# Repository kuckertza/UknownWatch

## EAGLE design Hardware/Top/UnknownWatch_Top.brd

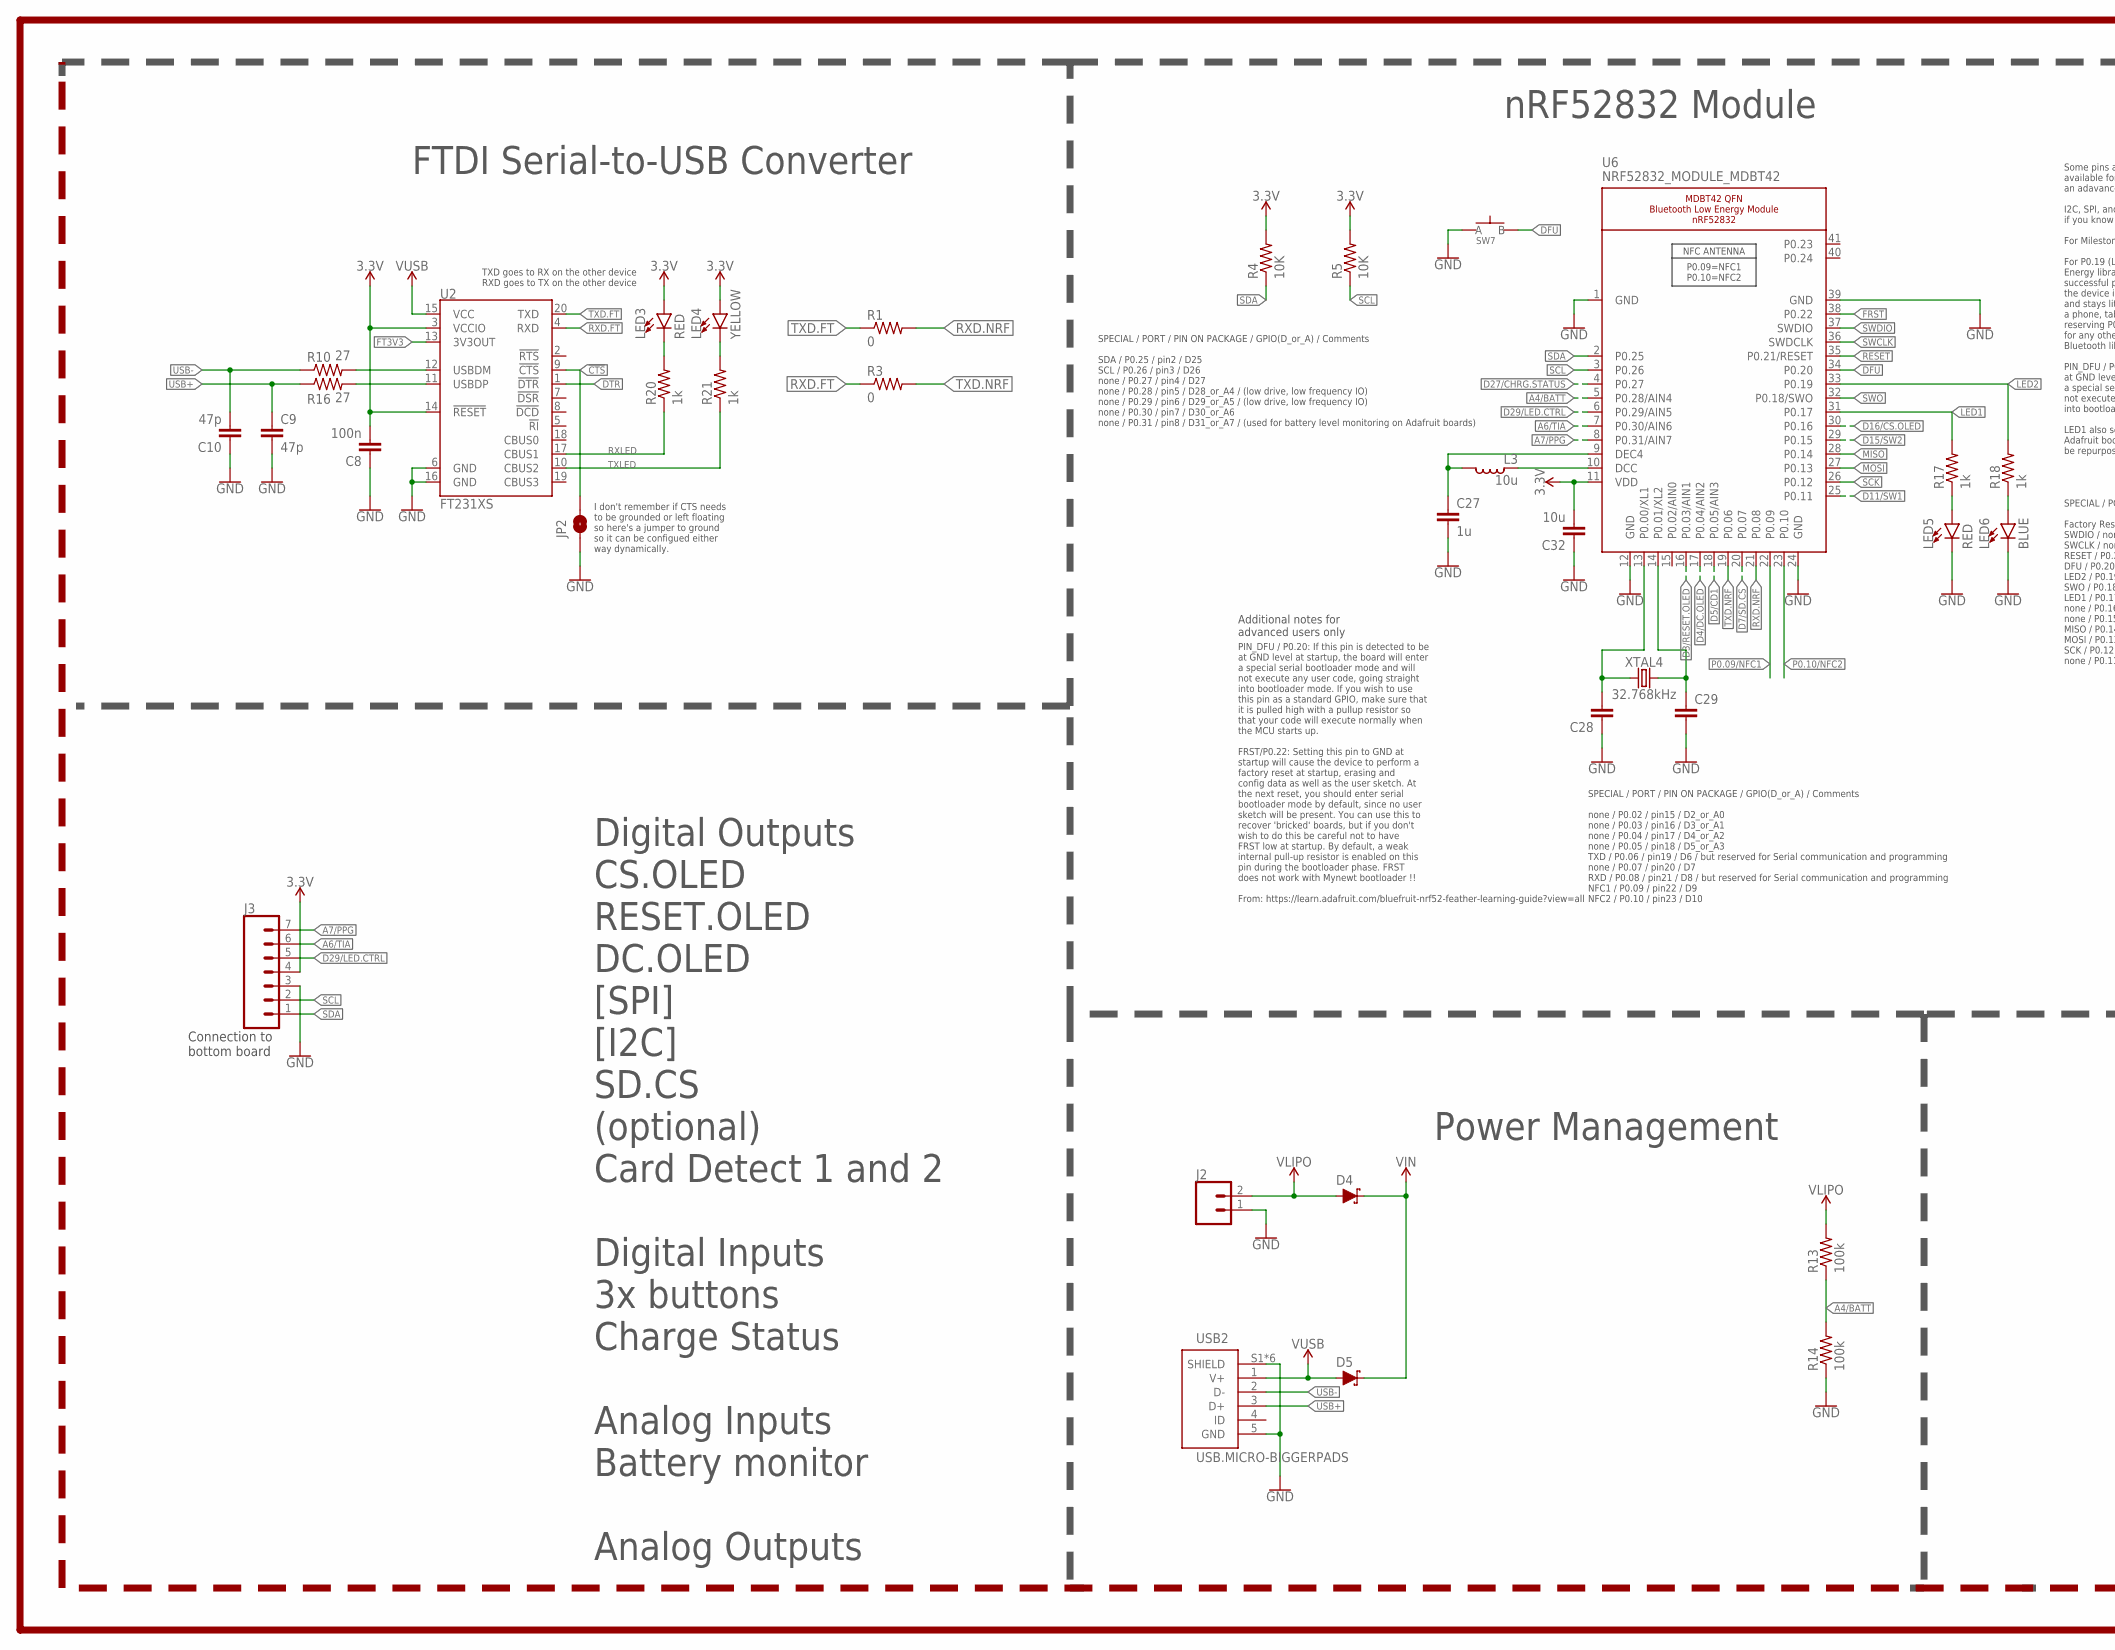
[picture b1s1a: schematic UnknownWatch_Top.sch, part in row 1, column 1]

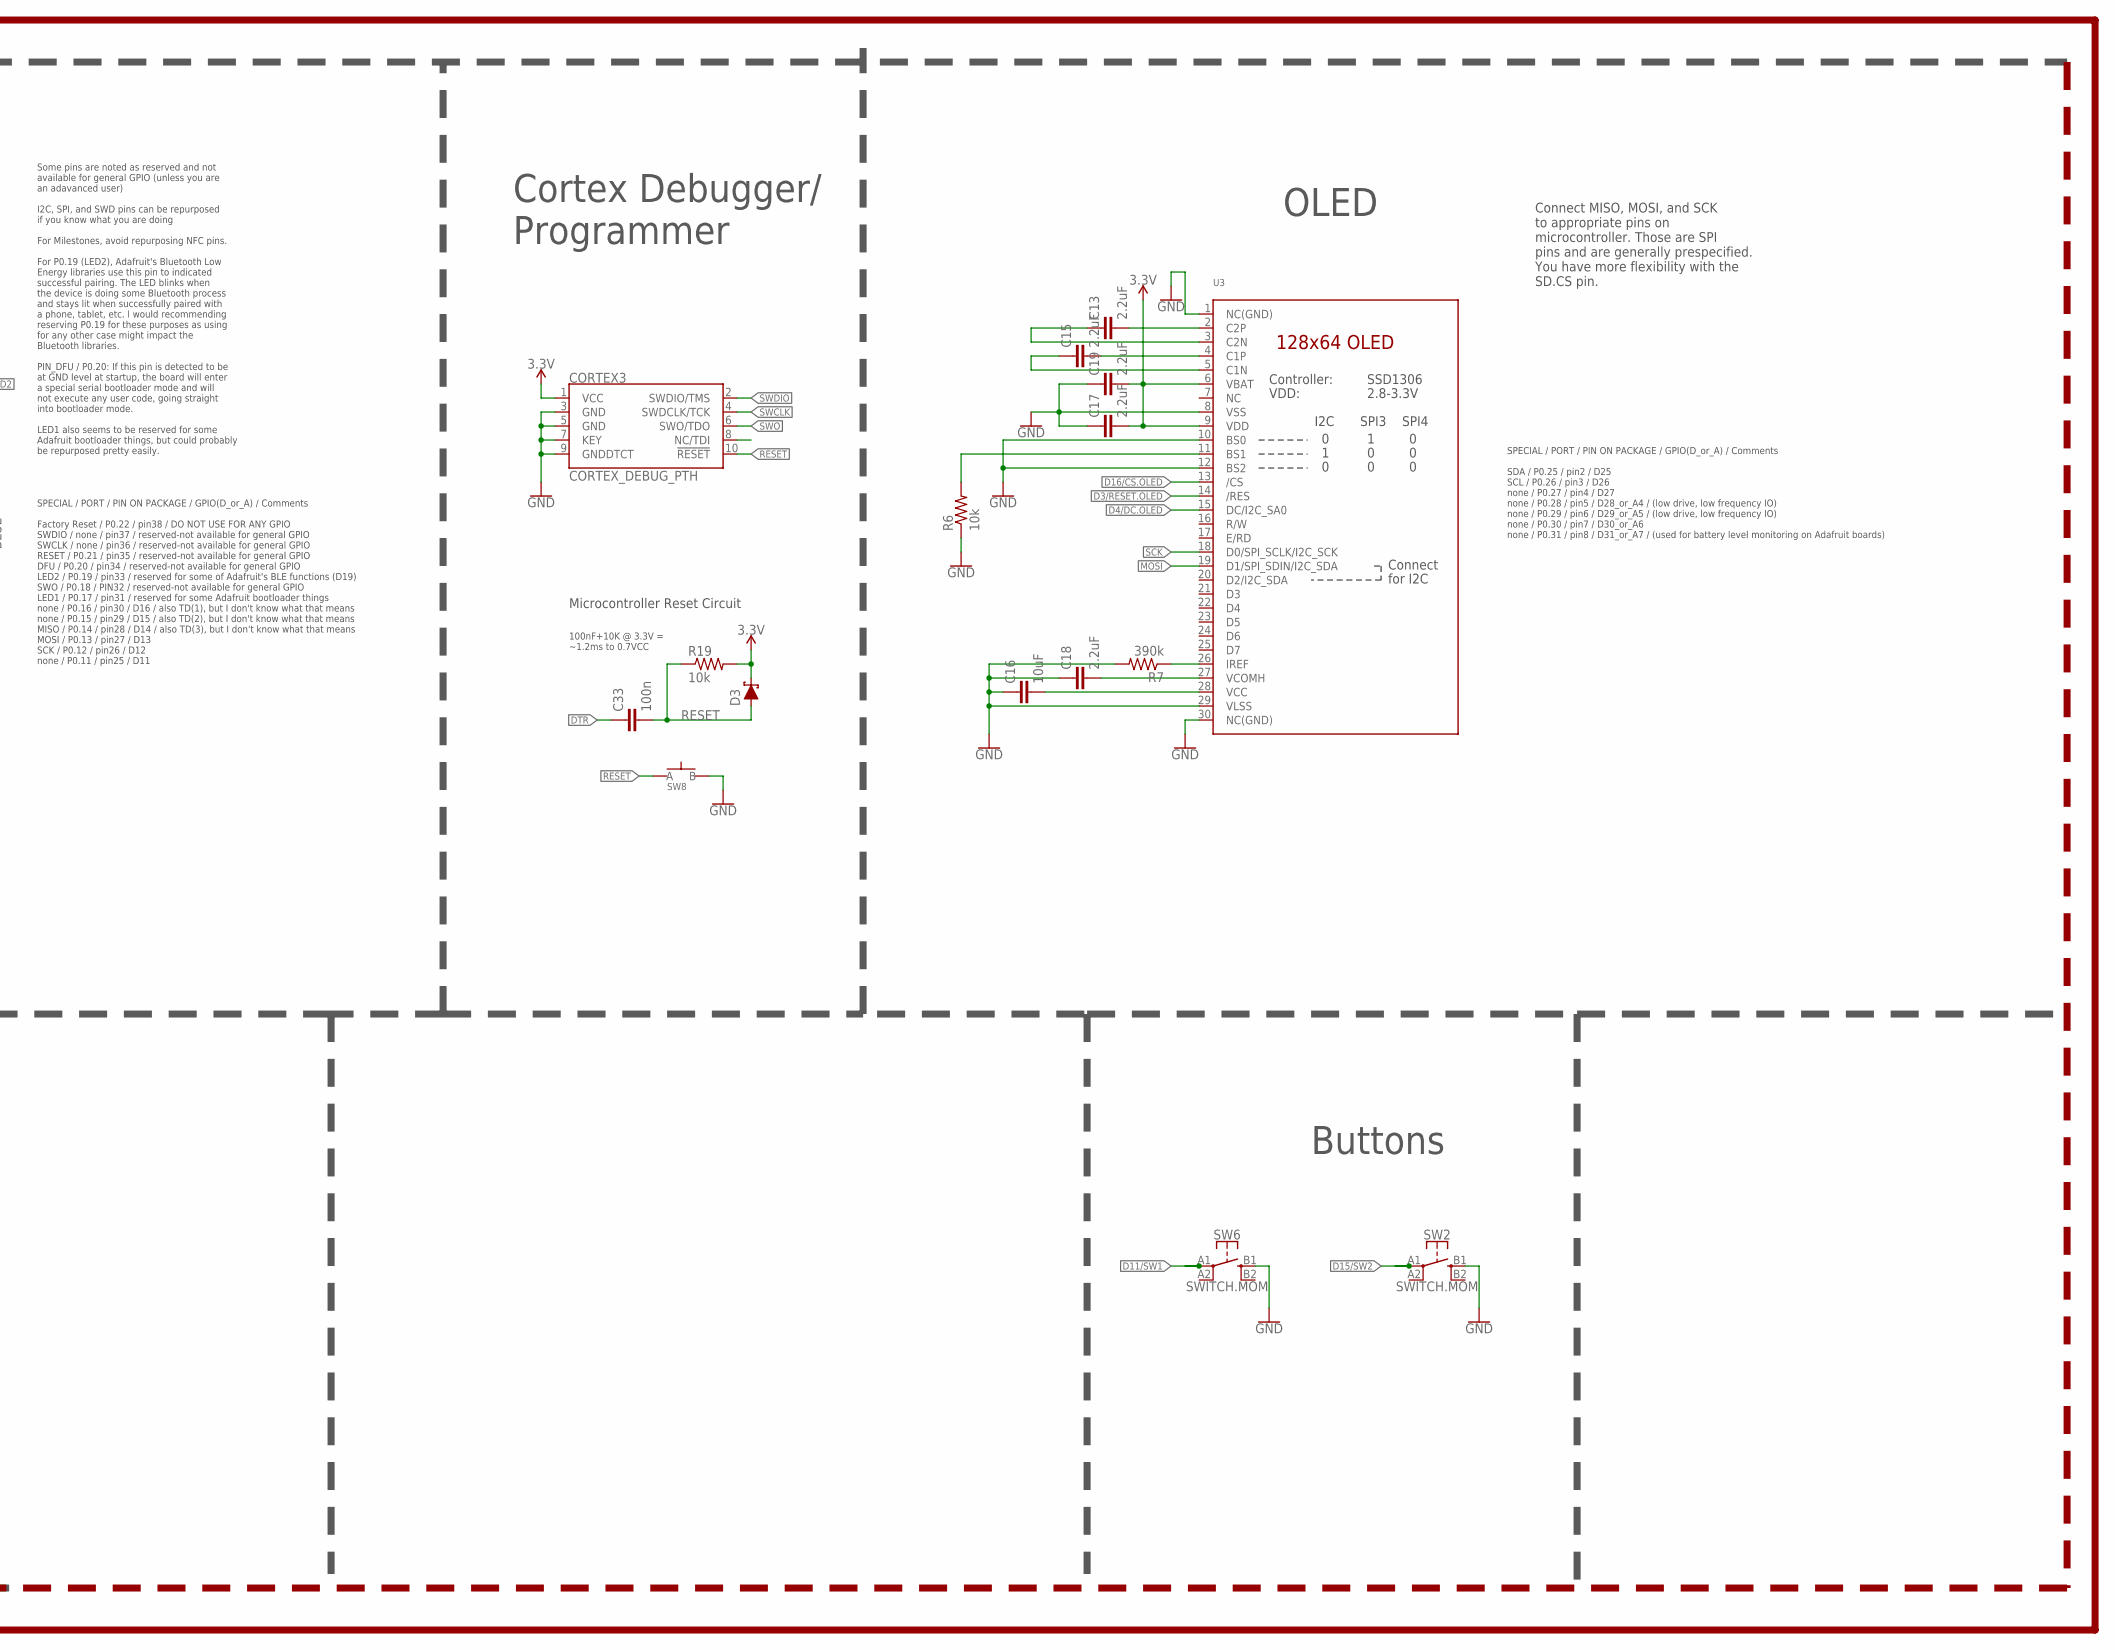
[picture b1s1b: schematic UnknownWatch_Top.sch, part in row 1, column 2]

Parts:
C8, C33: 100n; C0603
C9, C10: 47p; C0603
C13, C15, C17, C18, C19: 2.2uF; C0402
C16: 10uF; C0603
C27: 1u; C0603
C28, C29: CAPACITOR0603; C0603
C32: 10u; C0805
CORTEX3: CORTEX_DEBUG_PTH; 2X5-PTH-1.27MM
D3, D4, D5: SCHOTTKY-USC; USC
J2: CONN_02; 1X02
J3: CONN_07-1.27MM; 1X07_1.27MM
JP2: JUMPER-SMT_2_NO_SILK; SMT-JUMPER_2_NO_SILK
L3: 10u; L0603
LED3, LED5: RED; LED-0603
LED4: YELLOW; LED-0603
LED6: BLUE; LED-0603
R1, R3: 0; R0603
R4, R5: 10K; R0603
R6, R19: 10k; R0603
R7: 390k; R0603
R10, R16: 27; R0603
R13, R14: 100k; R0603
R17, R18, R20, R21: 1k; R0603
SW2, SW6: SWITCH.MOM; TACTILE_SWITCH_SMD_6.2MM_TALL
SW7, SW8: SPST-PTS830GG140-COPY.1-3; BUTTON-GULLWING
U2: FT231XS; SSOP20_L
U3: DISP_OLED_UG-2864HSWEG01-NO-WRAPAROUND; UG-2864HSWEG01_0.96IN_NO-WRAPAROUND
U6: NRF52832_MODULE_MDBT42; BLE_MODULE_RAYTAC_MDBT42
USB2: USB.MICRO-BIGGERPADS; USB-MICRO-01.BIGGERPADS
XTAL4: 32.768kHz; 2-SMD.NOLEAD.2.0MMTO1.2MM

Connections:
3.3V: C8.2, C17.2, C19.2, C32.2, CORTEX3.1 (VCC), D3.- (C), J3.4, LED3.A, LED4.A, R4.2, R5.2, R19.2, U2.3 (VCCIO), U2.14 (!RESET), U3.6 (VBAT), U3.9 (VDD), U6.11 (VDD)
!CTS: JP2.2, U2.9 (!CTS)
A4/BATT: R13.1, R14.2, U6.5 (P0.28/AIN4)
A6/TIA: J3.6, U6.7 (P0.30/AIN6)
A7/PPG: J3.7, U6.8 (P0.31/AIN7)
D3/RESET.OLED: U3.14 (/RES), U6.16 (P0.03/AIN1)
D4/DC.OLED: U3.15 (DC/I2C_SA0), U6.17 (P0.04/AIN2)
D5/CD1: U6.18 (P0.05/AIN3)
D7/SD.CS: U6.20 (P0.07)
D11/SW1: SW6.A1 (1), U6.25 (P0.11)
D15/SW2: SW2.A1 (1), U6.29 (P0.15)
D16/CS.OLED: U3.13 (/CS), U6.30 (P0.16)
D27/CHRG.STATUS: U6.4 (P0.27)
D29/LED.CTRL: J3.5, U6.6 (P0.29/AIN5)
DFU: SW7.3 (B), U6.34 (P0.20)
DTR: C33.1, U2.1 (!DTR)
FRST: U6.38 (P0.22)
FT3V3: U2.13 (3V3OUT)
GND: C8.1, C9.2, C10.1, C16.1, C17.1, C18.1, C19.1, C27.2, C28.1, C29.2, C32.1, CORTEX3.3 (GND), CORTEX3.5 (GND), CORTEX3.7 (KEY), CORTEX3.9 (GNDDTCT), J2.1, J3.3, JP2.1, LED5.C, LED6.C, R6.1, R7.2, R14.1, SW2.B1 (3), SW6.B1 (3), SW7.1 (A), SW8.3 (B), U2.6 (GND), U2.16 (GND), U3.1 (NC(GND)), U3.8 (VSS), U3.10 (BS0), U3.12 (BS2), U3.29 (VLSS), U3.30 (NC(GND)), U6.1 (GND), U6.12 (GND), U6.24 (GND), U6.39 (GND), USB2.5 (GND), USB2.S1 (SHIELD), USB2.S2 (SHIELD), USB2.S3 (SHIELD), USB2.S4 (SHIELD), USB2.S5 (SHIELD), USB2.S6 (SHIELD)
LED1: R17.2, U6.31 (P0.17)
LED2: R18.2, U6.33 (P0.19)
MISO: U6.28 (P0.14)
MOSI: U3.19 (D1/SPI_SDIN/I2C_SDA), U6.27 (P0.13)
unnamed: R6.2, U3.11 (BS1)
unnamed: R7.1, U3.26 (IREF)
unnamed: C13.2, U3.2 (C2P)
unnamed: C13.1, U3.3 (C2N)
unnamed: C15.2, U3.4 (C1P)
unnamed: C15.1, U3.5 (C1N)
unnamed: R10.2, U2.12 (USBDM)
unnamed: R16.2, U2.11 (USBDP)
unnamed: C16.2, U3.28 (VCC)
unnamed: LED3.C, R20.2
unnamed: C18.2, U3.27 (VCOMH)
unnamed: LED4.C, R21.2
unnamed: C28.2, U6.13 (P0.00/XL1), XTAL4.P$1 (1)
unnamed: C29.1, U6.14 (P0.01/XL2), XTAL4.P$2 (2)
unnamed: LED5.A, R17.1
unnamed: LED6.A, R18.1
unnamed: L3.1, U6.10 (DCC)
unnamed: C27.1, L3.2, U6.9 (DEC4)
P0.09/NFC1: U6.22 (P0.09)
P0.10/NFC2: U6.23 (P0.10)
RESET: C33.2, CORTEX3.10 (!RESET), D3.+ (A), R19.1, SW8.1 (A), U6.35 (P0.21/RESET)
RXD.FT: R3.1, U2.4 (RXD)
RXD.NRF: R1.2, U6.21 (P0.08)
RXLED: R20.1, U2.17 (CBUS1)
SCK: U3.18 (D0/SPI_SCLK/I2C_SCK), U6.26 (P0.12)
SCL: J3.2, R5.1, U6.3 (P0.26)
SDA: J3.1, R4.1, U6.2 (P0.25)
SWCLK: CORTEX3.4 (SWDCLK/TCK), U6.36 (SWDCLK)
SWDIO: CORTEX3.2 (SWDIO/TMS), U6.37 (SWDIO)
SWO: CORTEX3.6 (SWO/TDO), U6.32 (P0.18/SWO)
TXD.FT: R1.1, U2.20 (TXD)
TXD.NRF: R3.2, U6.19 (P0.06)
TXLED: R21.1, U2.10 (CBUS2)
USB+: C9.1, R16.1, USB2.3 (D+)
USB-: C10.2, R10.1, USB2.2 (D-)
VIN: D4.- (C), D5.- (C)
VLIPO: D4.+ (A), J2.2, R13.2
V_USB: D5.+ (A), U2.15 (VCC), USB2.1 (V+)

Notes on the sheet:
SPECIAL / PORT / PIN ON PACKAGE / GPIO(D_or_A) / Comments SDA / P0.25 / pin2 / D25 SCL / P0.26 / pin3 / D26 none / P0.27 / pin4 / D27 none / P0.28 / pin5 / D28_or_A4 / (low drive, low frequency IO) none / P0.29 / pin6 / D29_or_A5 / (low drive, low frequency IO) none / P0.30 / pin7 / D30_or_A6 none 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
Connect MISO, MOSI, and SCK to appropriate pins on microcontroller. Those are SPI pins and are generally prespecified. You have more flexibility with the SD.CS pin.
nRF52832 Module
OLED
Power Management
Buttons
Cortex Debugger/ Programmer
Digital Outputs CS.OLED RESET.OLED DC.OLED [SPI] [I2C] SD.CS (optional) Card Detect 1 and 2 Digital Inputs 3x buttons Charge Status Analog Inputs Battery monitor Analog Outputs
Microcontroller Reset Circuit
100nF+10K @ 3.3V = ~1.2ms to 0.7VCC
SPECIAL / PORT / PIN ON PACKAGE / GPIO(D_or_A) / Comments none / P0.02 / pin15 / D2_or_A0 none / P0.03 / pin16 / D3_or_A1 none / P0.04 / pin17 / D4_or_A2 none / P0.05 / pin18 / D5_or_A3 TXD / P0.06 / pin19 / D6 / but reserved for Serial communication and programming none / P0.07 / pin20 / D7 RXD / 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
SPECIAL / PORT / PIN ON PACKAGE / GPIO(D_or_A) / Comments Factory Reset / P0.22 / pin38 / DO NOT USE FOR ANY GPIO SWDIO / none / pin37 / reserved-not available for general GPIO SWCLK / none / pin36 / reserved-not available for general GPIO RESET / P0.21 / pin35 / reserved-not available for general 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
Some pins are noted as reserved and not available for general GPIO (unless you are an adavanced user) I2C, SPI, and SWD pins can be repurposed if you know what you are doing For Milestones, avoid repurposing NFC pins. For P0.19 (LED2), Adafruit's Bluetooth Low Energy libraries use this pin to indic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
PIN_DFU / P0.20: If this pin is detected to be at GND level at startup, the board will enter a special serial bootloader mode and will not execute any user code, going straight into bootloader mode. If you wish to use this pin as a standard GPIO, make sure that it is pulled high with a pullup resis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
Additional notes for advanced users only
TXD goes to RX on the other device RXD goes to TX on the other device
I don't remember if CTS needs to be grounded or left floating so here's a jumper to ground so it can be configued either way dynamically.
FTDI Serial-to-USB Converter
Connection to bottom board

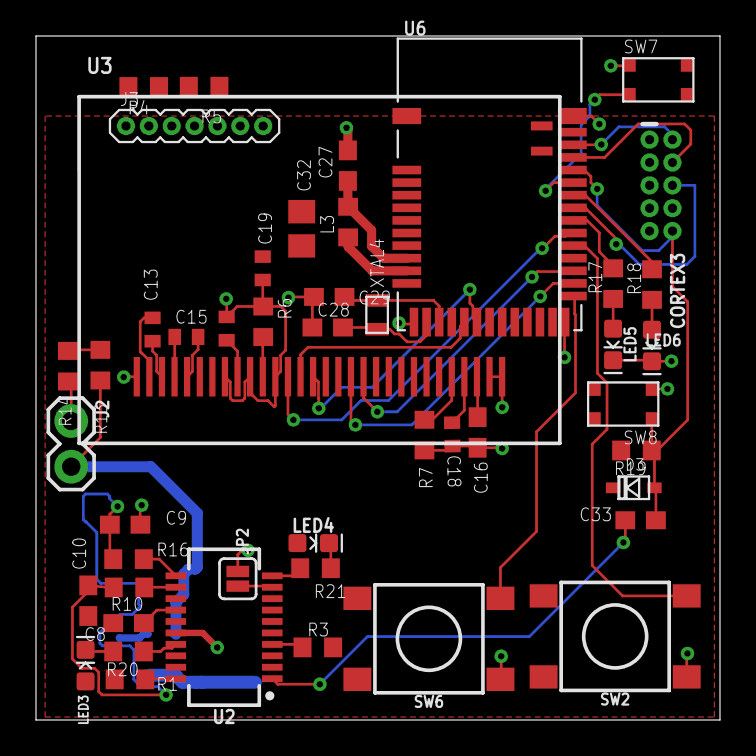
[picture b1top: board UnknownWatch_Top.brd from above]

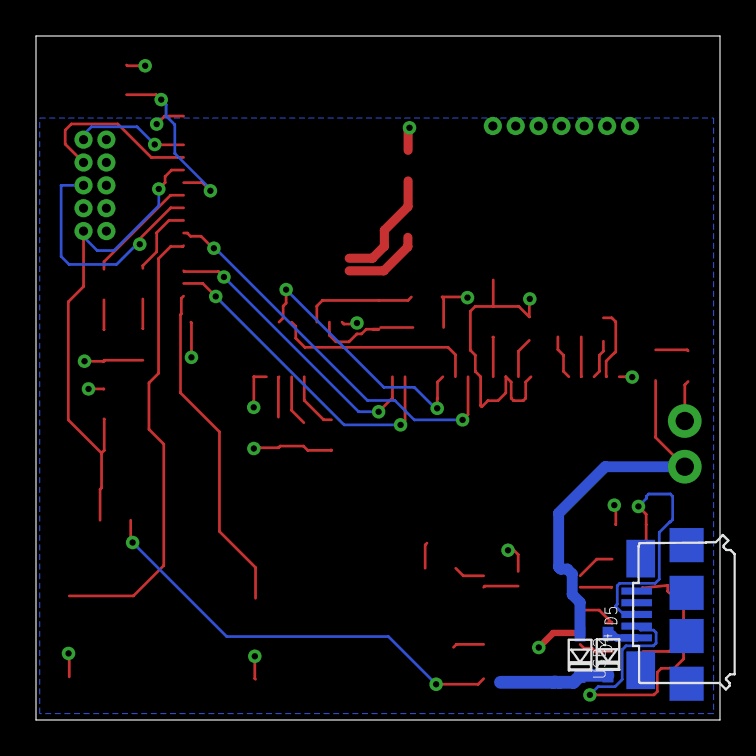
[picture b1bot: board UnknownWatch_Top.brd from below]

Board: 2 copper layers, 38.0 x 38.0 mm, 50 parts (3 on the bottom side), 53 nets.

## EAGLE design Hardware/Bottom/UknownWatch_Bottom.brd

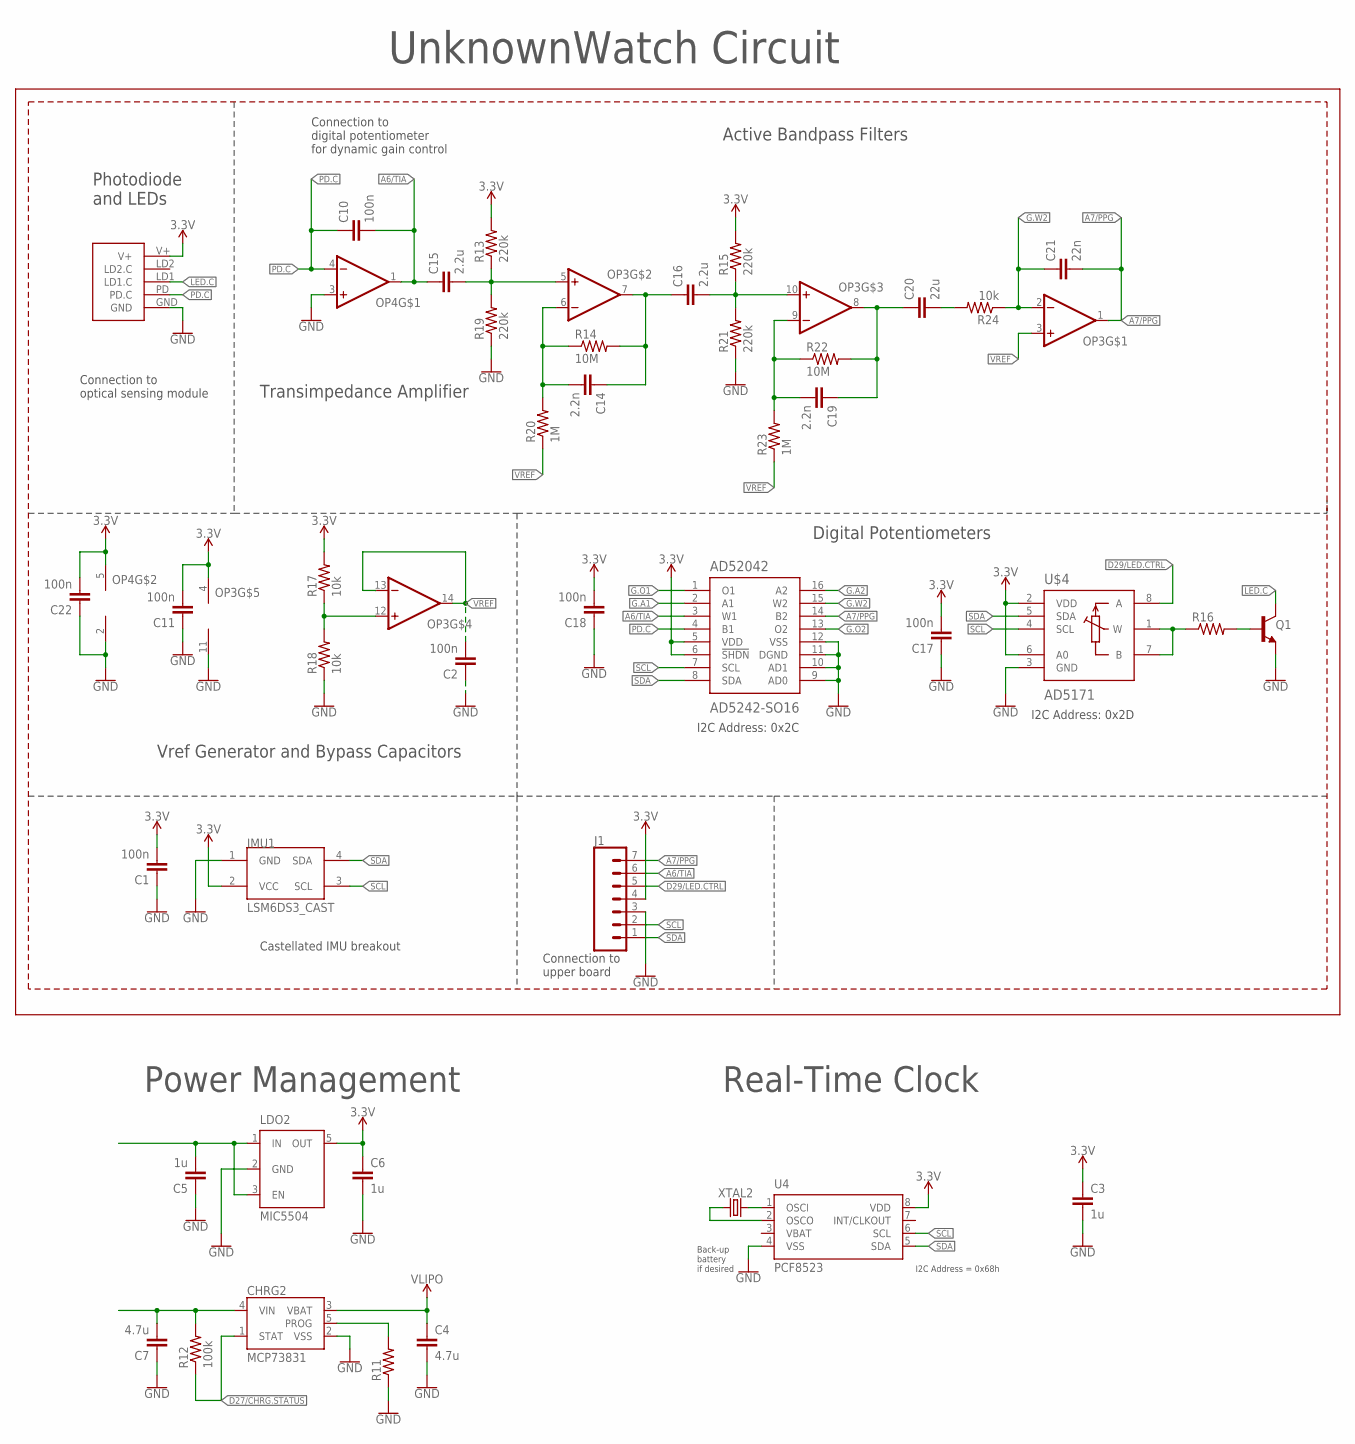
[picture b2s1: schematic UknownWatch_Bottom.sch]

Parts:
AD52042: AD5242-SO16; SO16
C1, C2, C10, C11, C17, C18, C22: 100n; C0603
C3, C5, C6: 1u; C0603
C4, C7: 4.7u; C0603
C14, C19: 2.2n; C0603
C15, C16: 2.2u; C0603
C20: 22u; C0603
C21: 22n; C0603
CHRG2: MCP73831; SOT23-5
IMU1: LSM6DS3_CAST
J1: CONN_07-1.27MM; 1X07_1.27MM
LDO2: MIC5504; SOT23-5
OP3: OP-QUAD-SO14; SO14
OP4: OP-SINGLEOT; SOT23-5
Q1: NPN-GENERIC; SOT23-3
R11, R16: RESISTOR0603; R0603
R12: 100k; R0603
R13, R15, R19, R21: 220k; R0603
R14, R22: 10M; R0603
R17, R18: 10k; R0402
R20, R23: 1M; R0603
R24: 10k; R0603
U4: PCF8523; SO8; DIGIKEY 568-5306-1-ND
U$3: PPG.MODULE.2
U$4: AD5171; SOT-23-8
XTAL2: 32.7680kHz; 2-SMD.NOLEAD.2.0MMTO1.2MM

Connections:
3.3V: AD52042.5 (VDD), AD52042.6 (!SHDN), C1.2, C3.1, C6.1, C11.2, C17.2, C18.2, C22.2, IMU1.2 (VCC), J1.4, LDO2.5 (OUT), OP3.4 (V+), OP4.5 (V+), R13.2, R15.2, R17.2, U4.8 (VDD), U$3.V+, U$4.2 (VDD), U$4.6 (A0)
A6/TIA: AD52042.3 (W1), C10.2, C15.1, J1.6, OP4.1 (OUT)
A7/PPG: AD52042.14 (B2), C21.2, J1.7, OP3.1 (OUT)
D27/CHRG.STATUS: CHRG2.1 (STAT), R12.1
D29/LED.CTRL: J1.5, U$4.8 (A)
G.A1: AD52042.2 (A1)
G.A2: AD52042.16 (A2)
G.O1: AD52042.1 (O1)
G.O2: AD52042.13 (O2)
G.W2: AD52042.15 (W2), C21.1, OP3.2 (-IN), R24.1
GND: AD52042.9 (AD0), AD52042.10 (AD1), AD52042.11 (DGND), AD52042.12 (VSS), C1.1, C2.1, C3.2, C4.2, C5.1, C6.2, C7.1, C11.1, C17.1, C18.1, C22.1, CHRG2.2 (VSS), IMU1.1 (GND), J1.3, LDO2.2 (GND), OP3.11 (V-), OP4.2 (V-), OP4.3 (+IN), Q1.2 (E), R11.1, R18.1, R19.1, R21.1, U4.4 (VSS), U$3.GND, U$4.3 (GND)
LED.C: Q1.3 (C), U$3.LD1 (LD1.C)
unnamed: U4.1 (OSCI), XTAL2.P$2 (2)
unnamed: CHRG2.5 (PROG), R11.2
unnamed: U4.2 (OSCO), XTAL2.P$1 (1)
unnamed: Q1.1 (B), R16.2
unnamed: R16.1, U$4.1 (W), U$4.7 (B)
unnamed: OP3.12 (+IN), R17.1, R18.2
unnamed: C15.2, OP3.5 (+IN), R13.1, R19.2
unnamed: C14.2, OP3.6 (-IN), R14.1, R20.2
unnamed: C14.1, C16.1, OP3.7 (OUT), R14.2
unnamed: C16.2, OP3.10 (+IN), R15.1, R21.2
unnamed: C19.2, OP3.9 (-IN), R22.1, R23.2
unnamed: C19.1, C20.1, OP3.8 (OUT), R22.2
unnamed: C20.2, R24.2
PD.C: AD52042.4 (B1), C10.1, OP4.4 (-IN), U$3.PD (PD.C)
SCL: AD52042.7 (SCL), IMU1.3 (SCL), J1.2, U4.6 (SCL), U$4.4 (SCL)
SDA: AD52042.8 (SDA), IMU1.4 (SDA), J1.1, U4.5 (SDA), U$4.5 (SDA)
VBAT: U4.3 (VBAT)
VIN: C5.2, C7.2, CHRG2.4 (VIN), LDO2.1 (IN), LDO2.3 (EN), R12.2
VLIPO: C4.1, CHRG2.3 (VBAT)
VREF: C2.2, OP3.3 (+IN), OP3.13 (-IN), OP3.14 (OUT), R20.1, R23.1

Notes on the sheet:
Photodiode and LEDs
Active Bandpass Filters
Digital Potentiometers
Transimpedance Amplifier
I2C Address: 0x2C
I2C Address: 0x2D
Vref Generator and Bypass Capacitors
Connection to optical sensing module
Connection to digital potentiometer for dynamic gain control
Connection to upper board
Castellated IMU breakout
UnknownWatch Circuit
Real-Time Clock
I2C Address = 0x68h
Back-up battery if desired
Power Management

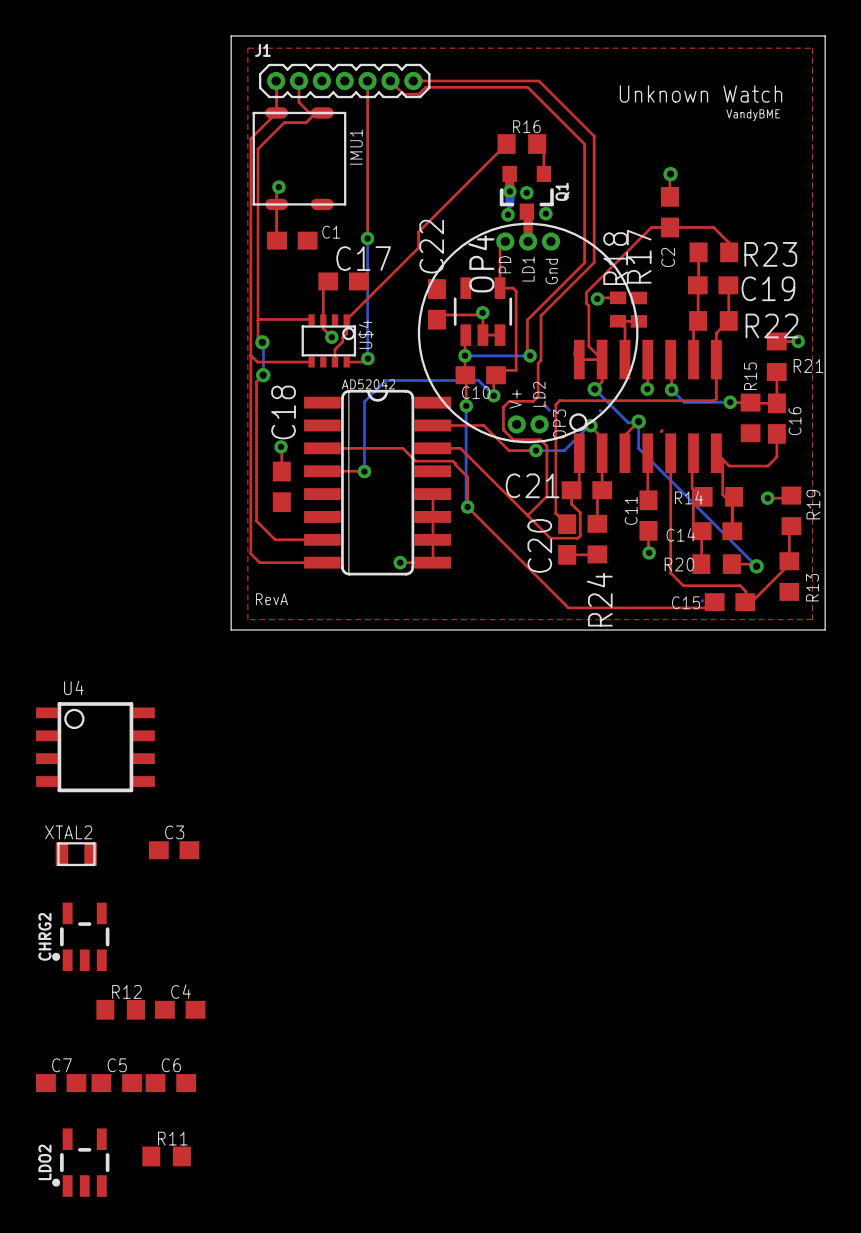
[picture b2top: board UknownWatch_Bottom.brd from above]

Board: 2 copper layers, 33.0 x 33.0 mm, 45 parts (0 on the bottom side), 27 nets.

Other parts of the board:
U$1: REV.A

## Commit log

2020-06-04 Added and Organized Files
2020-06-09 Added various compnents to top layer of device
2020-06-11 Adde Buttons
2020-06-11 Added segmentation and labels to schematic
2020-06-11 Put the labels in the right layer.
2020-06-11 Added a comment of all the pins that need to be kept track of.
2020-06-11 Made changes to buttons
2020-06-11 Deleted a button
2020-06-12 Added PPG and sized board
2020-06-18 Added connections from bottom to top board and other various changes.
2020-06-19 Made all changes associated wih take 002
2020-06-22 Worked on routing for bottom board.
2020-06-23 Made associated changes up to 41:07 in take 003.
2020-06-25 Wrote beggining of basic skeleton code
2020-06-25 Added .cpp file and .h file
2020-06-25 Routed more of the bottom board
2020-07-02 Worked on routing of bottom board
2020-07-02 Routed more of bottom board
2020-07-04 Finished bulk of routing on bottom board
2020-07-04 Finshed routing the bottom board except for airwire errors
2020-07-09 Began routing top board.
2020-07-17 Complted all routing of top board associated with take 4.
2020-07-23 Nearly finished routing top board
2020-08-07 Completed take 5 and did part of take 6.
